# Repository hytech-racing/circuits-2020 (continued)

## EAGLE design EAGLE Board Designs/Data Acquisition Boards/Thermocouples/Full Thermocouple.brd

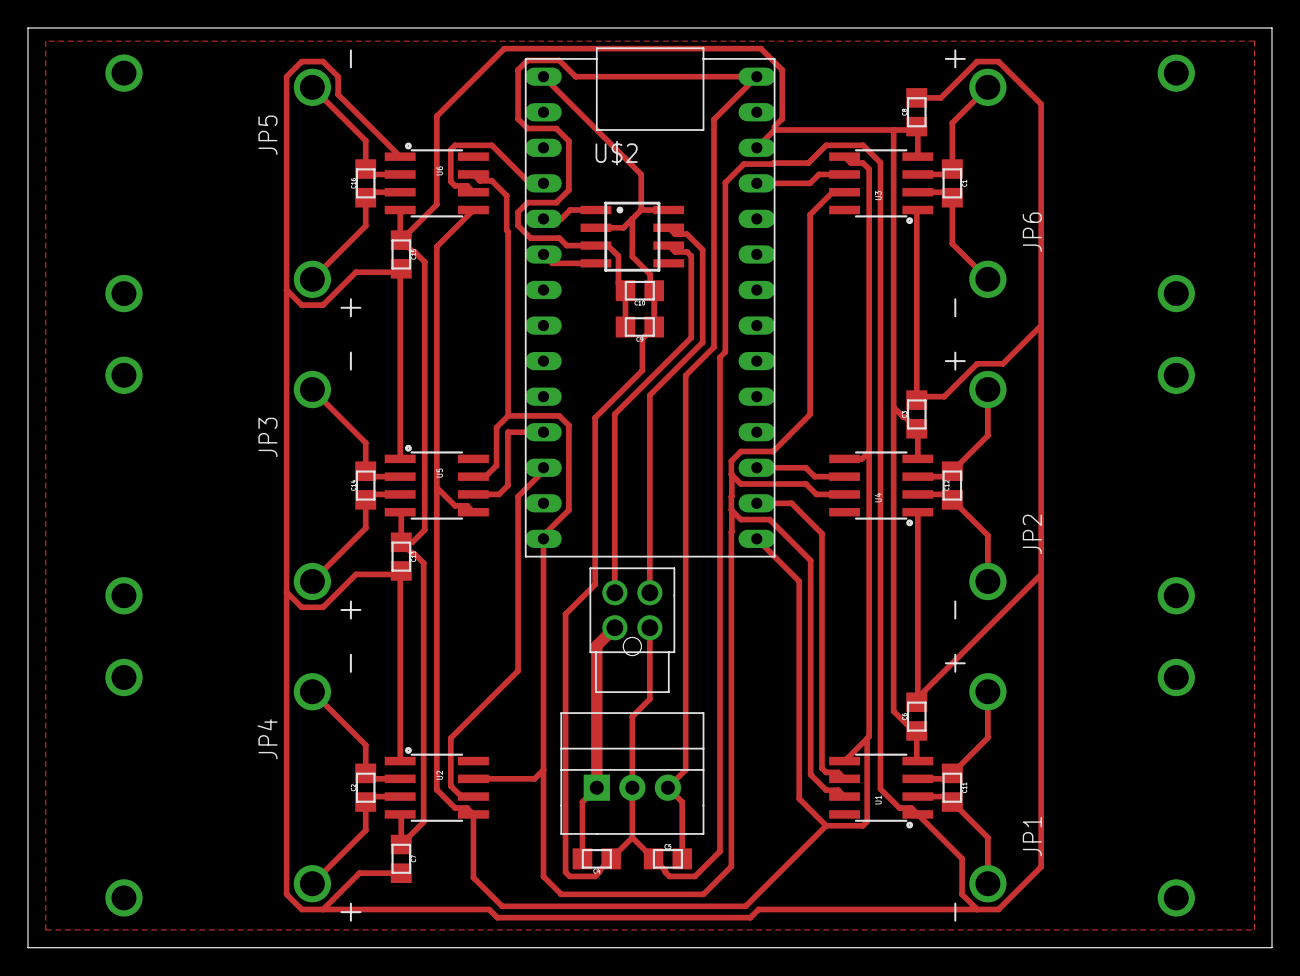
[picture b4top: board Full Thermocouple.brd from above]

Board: 2 copper layers, 88.9 x 65.7 mm, 32 parts (0 on the bottom side), 28 nets.

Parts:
C1, C2, C11, C12, C14, C16: 10 nF; 0805
C3, C6, C7, C8, C9, C13, C15: .1 uF; 0805
C4, C5: 10uF; 0805
C10: 1 uF; 0805
JP1, JP2, JP3, JP4, JP5, JP6: PCB_THERMOCOUPLE; PCC-SMP
REG: 5V; OKI-78SR
U1, U2, U3, U4, U5, U6: MAX31855K; SOIC8
U$1: TEENSY_3.2_SIMPLE
U$2: MCP2551; SOIC-08
X7: CONNECTOR-4NANO-FIT-VERTICAL-4; NANO-FIT_VERTICAL-4

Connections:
3.3V: C3.1, C6.1, C7.1, C8.1, C13.1, C15.1, U1.4, U2.4, U3.4, U4.4, U5.4, U6.4, U$1.3.3V
5V: C5.2, C9.2, C10.2, REG.3, U$1.VIN, U$2.3
+12V: C4.2, REG.1, X7.P$1
CANH: U$2.7, X7.P$4
CANL: U$2.6, X7.P$3
GND: C3.2, C4.1, C5.1, C6.2, C7.2, C8.2, C9.1, C10.1, C13.2, C15.2, REG.2, U1.1, U2.1, U3.1, U4.1, U5.1, U6.1, U$1.GND, U$2.2, U$2.8, X7.P$2
MISO: U1.7, U2.7, U3.7, U4.7, U5.7, U6.7, U$1.D12
unnamed: U$1.D3(CANTX), U$2.1
unnamed: C16.1, JP5.+, U6.3
unnamed: C11.2, JP1.-, U1.2
unnamed: C16.2, JP5.-, U6.2
unnamed: C12.1, JP2.+, U4.3
unnamed: C2.1, JP4.+, U2.3
unnamed: C11.1, JP1.+, U1.3
unnamed: C12.2, JP2.-, U4.2
unnamed: C2.2, JP4.-, U2.2
unnamed: U$1.D4(CANRX), U$2.4
unnamed: C1.1, JP6.+, U3.3
unnamed: C1.2, JP6.-, U3.2
unnamed: C14.1, JP3.+, U5.3
unnamed: C14.2, JP3.-, U5.2
SCK: U1.5, U2.5, U3.5, U4.5, U5.5, U6.5, U$1.D13
T1: U1.6, U$1.A0
T2: U4.6, U$1.A1
T3: U3.6, U$1.A9
T4: U2.6, U$1.D10(TX2)
T5: U5.6, U$1.D9(RX2)
T6: U6.6, U$1.D2

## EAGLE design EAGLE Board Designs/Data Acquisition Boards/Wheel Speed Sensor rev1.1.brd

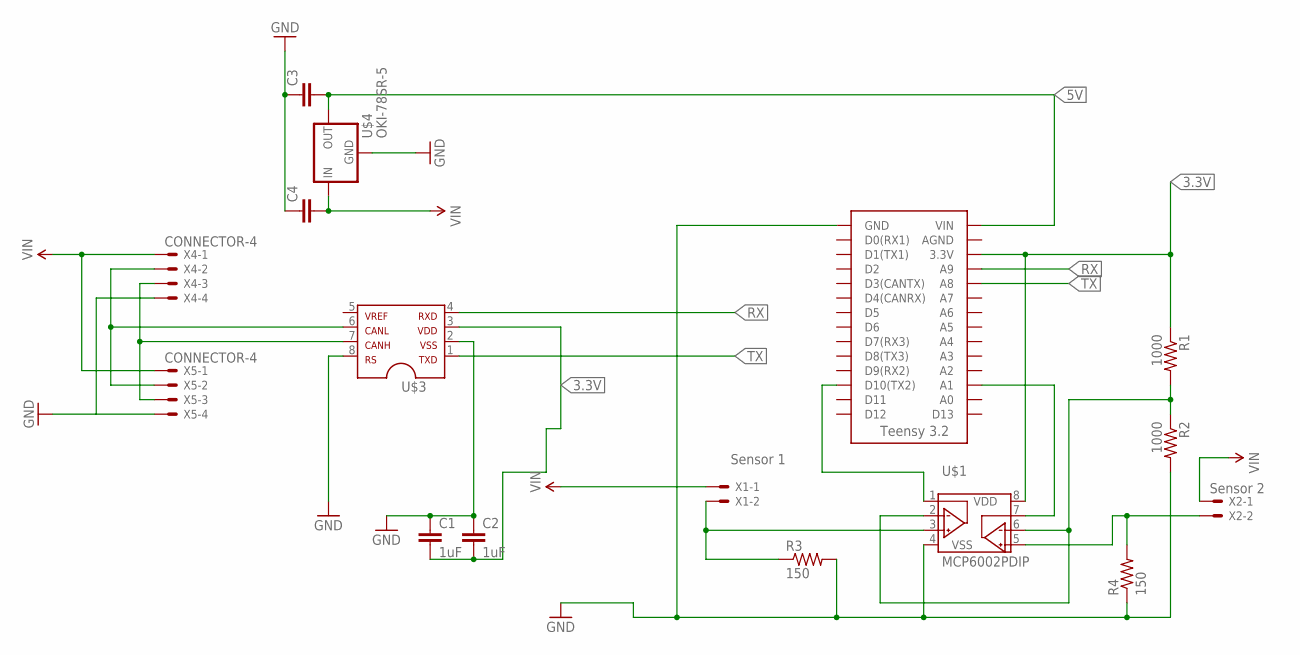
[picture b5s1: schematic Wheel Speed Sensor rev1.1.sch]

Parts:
C1, C2: 1uF; CAP-PTH-SMALLEZ
C3, C4: CAPEZ; CAP-PTH-SMALLEZ
R1, R2: 1000; AXIAL-0.3
R3, R4: 150; AXIAL-0.3
U$1: MCP6002PDIP; DIL08
U$2: TEENSY_3.2_SIMPLE
U$3: MCP2551DIL; DIL08
U$4: OKI-78SR-5; OKI-78SR
X1: Sensor 1; MINIFIT_5566-2
X2: Sensor 2; MINIFIT_5566-2
X4, X5: CONNECTOR-4; MINIFIT_5566-4

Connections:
3.3V: C1.2, C2.2, R1.P$1 (1), U$1.8 (VDD), U$2.3.3V, U$3.3
5V: C3.2, U$2.VIN, U$4.3 (OUT)
CANH: U$3.7, X4.3, X5.3
GND: C1.1, C2.1, C3.1, C4.1, R2.P$2 (2), R3.P$2 (2), R4.P$1 (1), U$1.4 (VSS), U$2.GND, U$3.2, U$3.8, U$4.2 (GND), X4.4, X5.4
unnamed: R1.P$2 (2), R2.P$1 (1), U$1.2 (VINA-), U$1.6 (VINB-)
unnamed: U$3.6, X4.2, X5.2
unnamed: R3.P$1 (1), U$1.3 (VINA+), X1.2
unnamed: U$1.7 (VOUTB), U$2.A1
unnamed: U$1.1 (VOUTA), U$2.D10(TX2)
unnamed: R4.P$2 (2), U$1.5 (VINB+), X2.2
RX: U$2.A9, U$3.4
TX: U$2.A8, U$3.1
VIN: C4.2, U$4.1 (IN), X1.1, X2.1, X4.1, X5.1

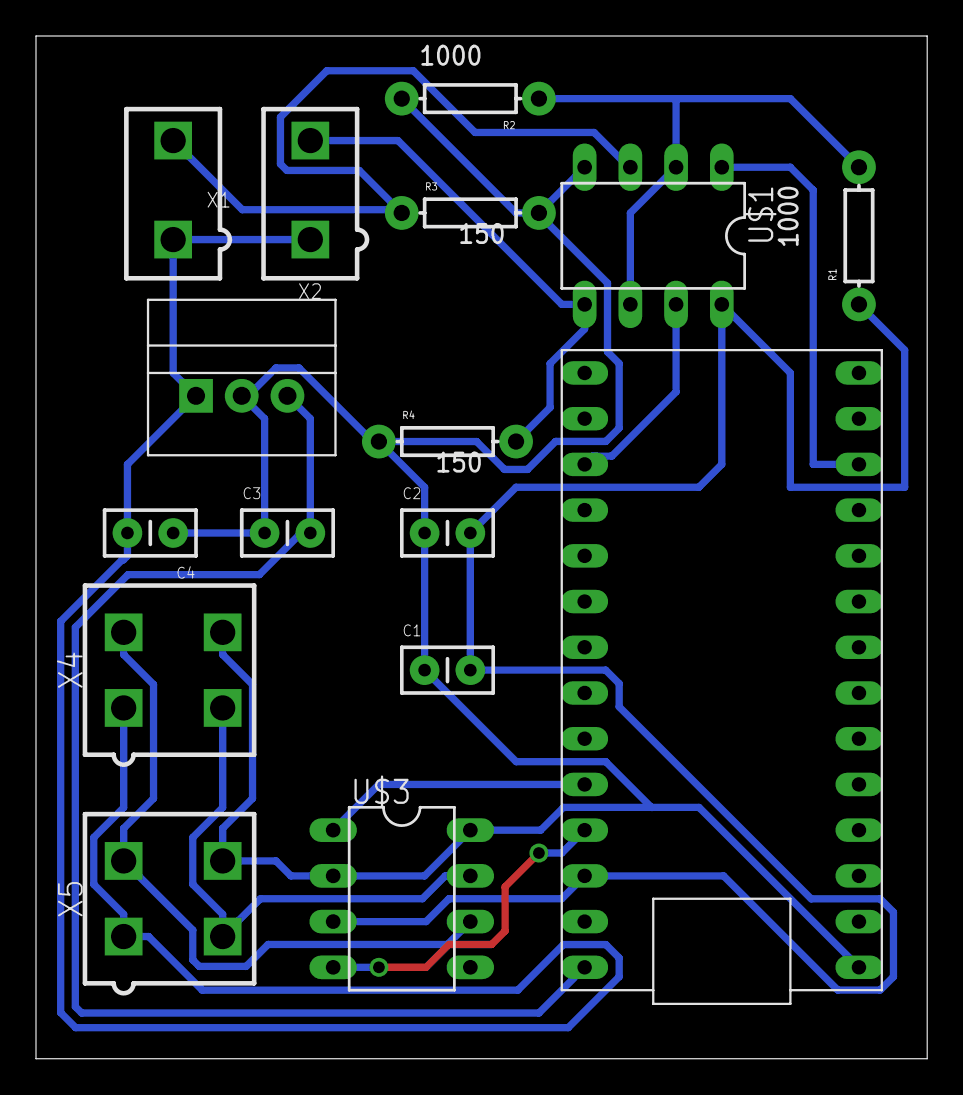
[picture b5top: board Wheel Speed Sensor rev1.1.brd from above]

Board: 2 copper layers, 49.5 x 56.8 mm, 16 parts (0 on the bottom side), 13 nets.
